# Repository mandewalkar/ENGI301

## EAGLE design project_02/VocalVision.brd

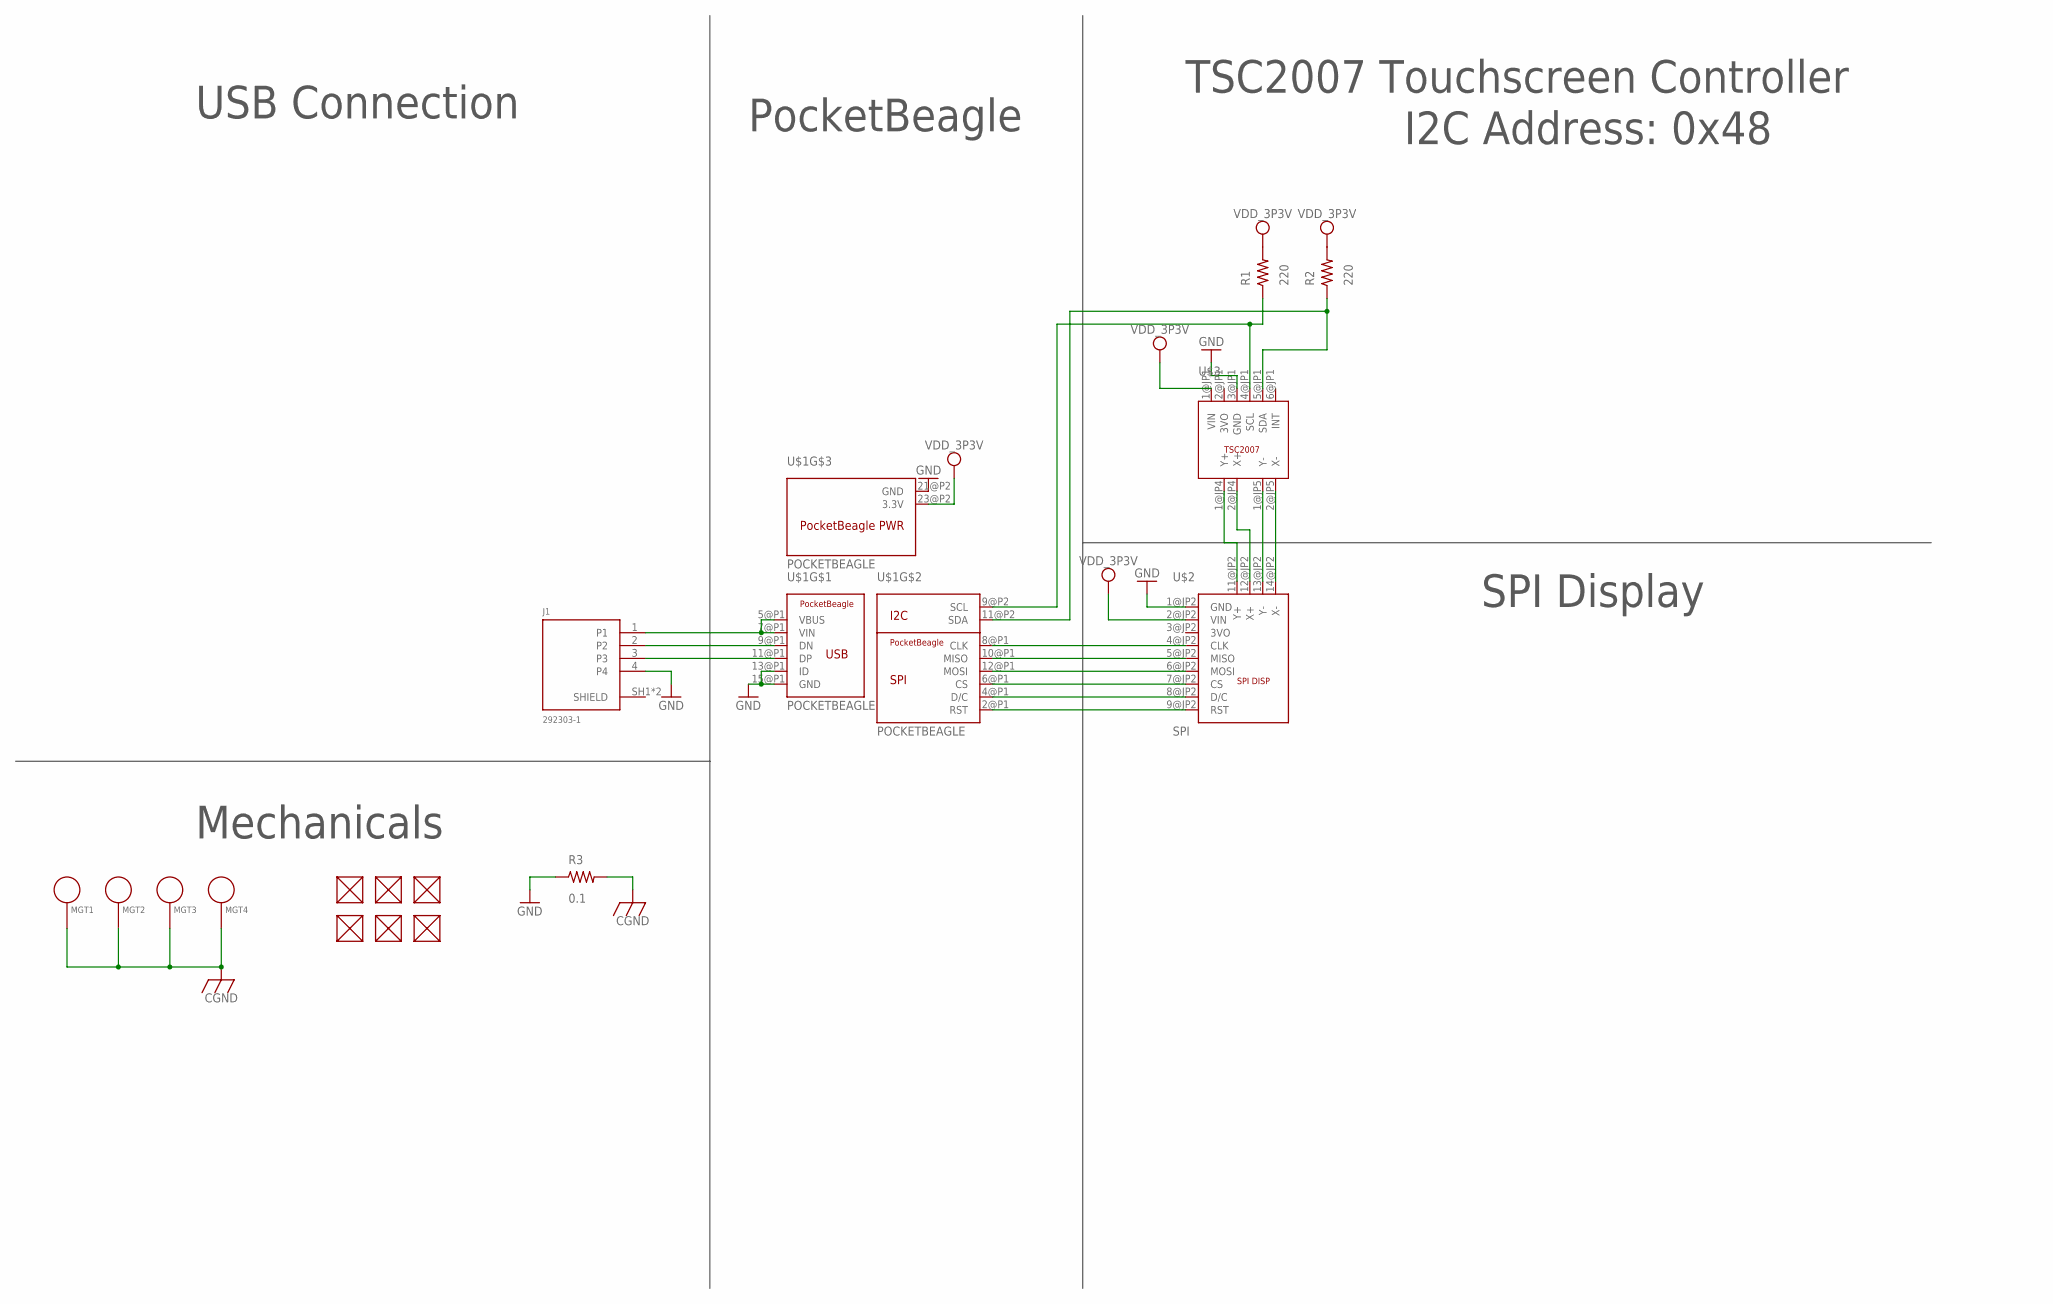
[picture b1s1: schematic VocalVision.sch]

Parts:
FUD1, FUD2, FUD3, FUD4, FUD5, FUD6: FIDUCIAL; FIDUCIAL_40MIL
J1: 292303-1; TE_292303-1
MGT1, MGT2, MGT3, MGT4: MOUNTING_HOLE
R1, R2: 220; R0603
R3: 0.1; R0603
U$1: POCKETBEAGLE
U$2: SPI
U$3: TSC2007

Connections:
CGND: MGT1.P$1, MGT2.P$1, MGT3.P$1, MGT4.P$1, R3.2
GND: J1.4, R3.1, U$1.13@P1 (ID), U$1.15@P1 (GND), U$1.21@P2 (GND), U$2.1@JP2 (GND), U$3.3@JP1 (GND)
unnamed: R2.1, U$1.11@P2 (SDA), U$3.5@JP1 (SDA)
unnamed: R1.1, U$1.9@P2 (SCL), U$3.4@JP1 (SCL)
unnamed: U$1.8@P1 (CLK), U$2.4@JP2 (CLK)
unnamed: U$1.10@P1 (MISO), U$2.5@JP2 (MISO)
unnamed: J1.1, U$1.5@P1 (VBUS), U$1.7@P1 (VIN)
unnamed: J1.2, U$1.9@P1 (DN)
unnamed: J1.3, U$1.11@P1 (DP)
unnamed: U$1.12@P1 (MOSI), U$2.6@JP2 (MOSI)
unnamed: U$1.6@P1 (CS), U$2.7@JP2 (CS)
unnamed: U$1.4@P1 (D/C), U$2.8@JP2 (D/C)
unnamed: U$1.2@P1 (RST), U$2.9@JP2 (RST)
unnamed: U$2.14@JP2 (X-), U$3.2@JP5 (X-)
unnamed: U$2.13@JP2 (Y-), U$3.1@JP5 (Y-)
unnamed: U$2.11@JP2 (Y+), U$3.1@JP4 (Y+)
unnamed: U$2.12@JP2 (X+), U$3.2@JP4 (X+)
VDD_3P3V: R1.2, R2.2, U$1.23@P2 (3.3V), U$2.2@JP2 (VIN), U$3.1@JP1 (VIN)

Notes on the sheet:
TSC2007 Touchscreen Controller
SPI Display
PocketBeagle
USB Connection
Mechanicals
I2C Address: 0x48

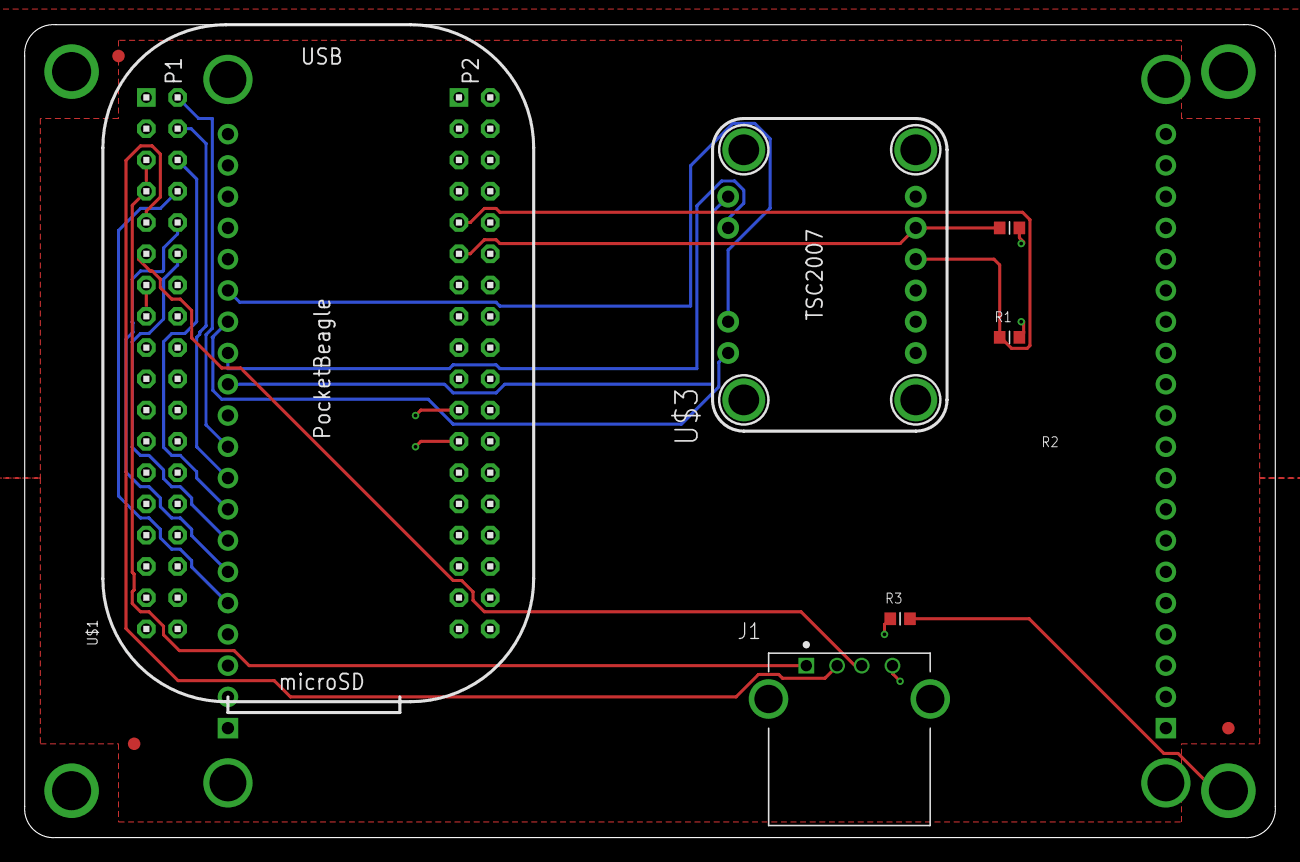
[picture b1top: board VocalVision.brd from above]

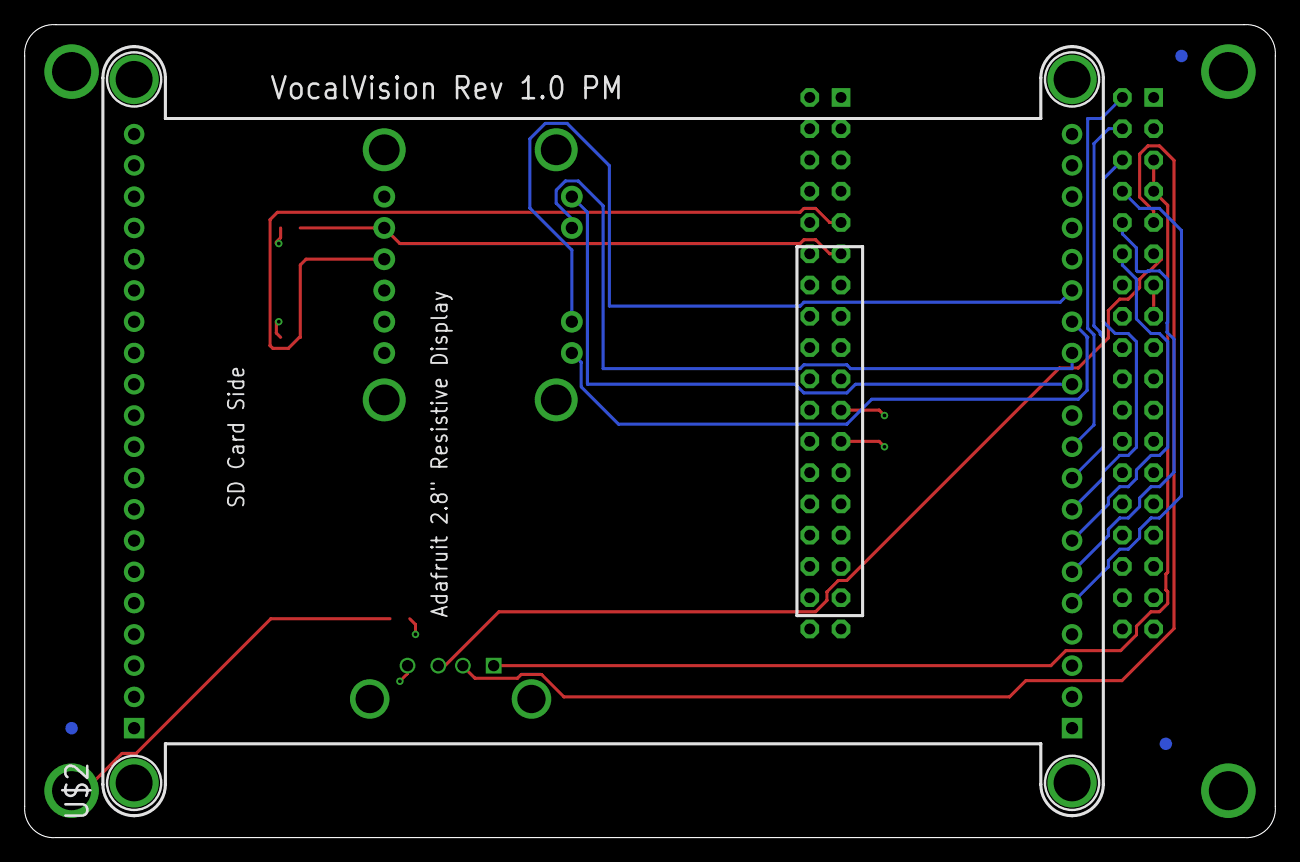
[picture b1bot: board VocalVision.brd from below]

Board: 4 copper layers, 101.6 x 66.1 mm, 17 parts (4 on the bottom side), 18 nets.

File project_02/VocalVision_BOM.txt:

Partlist exported from C:/Users/parni/Downloads/PCB/VocalVision/VocalVision.sch at 12/12/2023 2:49 PM

Qty Value         Device        Package        Parts                              Description                                        AVAILABILITY CENTERLINE_PITCH CHECK_PRICES                                                                             COMMENT  DESCRIPTION                                                                                    EU_ROHS_COMPLIANCE MF              MP       NUMBER_OF_POSITIONS PACKAGE PRICE PRODUCT_TYPE PURCHASE-URL                                                                                                                               SNAPEDA_LINK                                                                             
1   0.1           R_R0603       R0603          R3                                 RESISTOR, American symbol                                                                                                                                                                                                                                                                                                                                                                                                                                                                                                                                                                                        
2   220           R_R0603       R0603          R1, R2                             RESISTOR, American symbol                                                                                                                                                                                                                                                                                                                                                                                                                                                                                                                                                                                        
1   292303-1      292303-1      TE_292303-1    J1                                 CONN USB RECEPT R/A TYPE A 4POS Check availability In Stock     2 mm[.078 in]    https://www.snapeda.com/parts/292303-1/TE+Connectivity+AMP+C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 292303-1  Type A Standard USB Connector 4 Position Right Angle Mount 1 Port | TE Connectivity 292303-1  Compliant          TE Connectivity 292303-1 4                   None    None  Connector    https://www.snapeda.com/api/url_track_click_mouser/?unipart_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 Connectivity&part_name=292303-1&search_term=292303-1 https://www.snapeda.com/parts/292303-1/TE+Connectivity+AMP+C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
6   FIDUCIAL      FIDUCIAL      FIDUCIAL_40MIL FUD1, FUD2, FUD3, FUD4, FUD5, FUD6                                                                                                                                                                                                                                                                                                                                                                                                                                                                                                                                                                                                                  
4   MOUNTING_HOLE MOUNTING_HOLE MOUNTING_HOLE  MGT1, MGT2, MGT3, MGT4             Chassis Mounting Hole w/GND connection ability                                                                                                                                                                                                                                                                                                                                                                                                                                                                                                                                                                   
1   POCKETBEAGLE  POCKETBEAGLE  POCKETBEAGLE   U$1                                                                                                                                                                                                                                                                                                                                                                                                                                                                                                                                                                                                                                                 
1   SPI           SPI           SPI            U$2                                                                                                                                                                                                                                                                                                                                                                                                                                                                                                                                                                                                                                                 
1   TSC2007       TSC2007       TSC2007        U$3

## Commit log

2023-09-12 First commit!
2023-09-27 Create hello
2023-09-27 Create simplecalc
2023-09-27 added extra functionality
2023-09-27 fixed invalid input error
2023-09-27 edit2
2023-09-27 edit3
2023-09-27 original, need to ask about error
2023-09-27 added py2 compatibility
2023-09-27 added the new operators into input prompt
2023-09-28 functionality for shift with int
2023-09-28 blink led
2023-09-28 added licensing and docstring
2023-09-28 fixed to be 5hz
2023-09-28 button stuff
2023-09-28 button done
2023-10-04 screen code
2023-10-13 preliminary software diagram
2023-10-20 new file transfer from local
2023-11-06 display files
2023-11-07 sample touch code
2023-11-07 touch and display
2023-11-07 logo
2023-11-10 experiments
2023-11-13 lots of changes
2023-11-14 recorder
2023-11-14 watson
2023-11-14 ui done
2023-11-14 working analysis!
2023-11-15 final working code, no comments
2023-11-15 networking code
2023-11-19 adding comments and docs
2023-11-19 finals
